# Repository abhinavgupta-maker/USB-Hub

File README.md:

# USB-Hub

# Zine

# Description
So this is my USB Hub 2.0 which has 2x Usb-A and 2x Type-C port and 1x Type-C for upstream which has a retro game controller case which makes it look good and what makes it special is that it is really small like 50 x 30 mm (approx) which makes it really good for storing it.

# How to build it
firstly extract the gerber files of the pcb and upload it on a website and make sure to select PCBA but if you can solder the things on your own then get the pcb only and then get the case 3d printed you can customize it on your own if you want and tehn get it 3d printed.

# Why I built this
For my own usage so that i can extend my ports on the laptop while coding and or playing games.

# Usage
I would use it for for my laptop as it only has 2 USB-A in which one is occupied by cooling stand and other by the mouse so i need to have more ports where i can connect my kbm and my microcontroller while i am coding. and i can use it on my fathers tab to connect a physical keyboard and mouse.

# Schematic

# PCB

# CAD

# BOM

|Product Name        |Product  Link                                                                                                                                                                              |Unit Price|Amount|
|--------------------|-------------------------------------------------------------------------------------------------------------------------------------------------------------------------------------------|----------|------|
|                    |                                                                                                                                                                                           |          |      |
|SMD capacitors 100nF|https://jlcpcb.com/partdetail/YAGEO-CC0603KRX7R9BB104/C14663                                                                                                                               |$0.0094   |11    |
|SMD Resistors 10K   |https://quartzcomponents.com/products/10k-ohm-103-5-smd-resistor-0805-pack-of-20-pieces                                                                                                    |$0.11     |6     |
|SL2.1S              |https://www.lcsc.com/product-detail/C2684433.html?s_z=n_q_SL2.1S&spm=wm.fly.bg.0.xh&lcsc_vid=FQQKBFAFRQVdBABTRQNcBQdWTgRZUlEATgdZAwUHRgMxVlNeRlRcVlVWQ1lfVTsOAxUeFF5JWBYZEEoKFBINSQcJGk4%3D|$9.04     |1     |
|Type-C Port         |https://jlcpcb.com/partdetail/SHOUHAN-TYPEC16PIN/C393939                                                                                                                                   |$0.07     |3     |
|USB-A port          |https://jlcpcb.com/partdetail/SHOUHAN-10_0_QHHTZB63/C668591                                                                                                                                |$0.0662   |2     |
|                    |                                                                                                                                                                                           |          |      |
|                    |Total:                                                                                                                                                                                     |10$ Approx|      |

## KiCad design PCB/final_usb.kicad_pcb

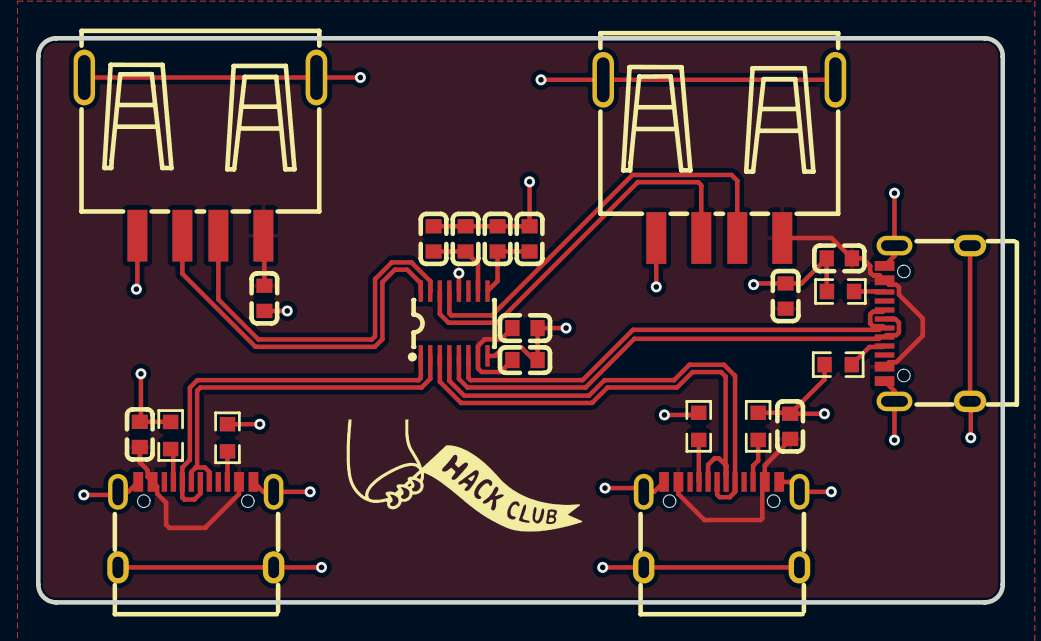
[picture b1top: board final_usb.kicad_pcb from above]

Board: 2 copper layers, 53.6 x 31.3 mm, 23 parts (0 on the bottom side), 20 nets.

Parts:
C1, C2, C3, C4, C5, C6, C7, C8, C9, C10, C11: C0603
R1, R2, R3, R4, R5, R6: R0603
U1: SSOP-16_L4.6-W2.6-P0.53-LS4.0-BL
USB1, USB5, USB6: USB-C-SMD_TYPE-C-16PIN-2MD-073
USB2, USB3: USB-A-TH_10.0QHHTZB6.3

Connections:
$1N1194: R1.2, USB6.A5
$1N1220: R2.2, USB6.B5
$1N1246: R3.2, USB5.A5
$1N1298: R5.2, USB1.B5
$1N1324: R6.2, USB1.A5
$1N2853: C7.1, C8.1, U1.9
$1N2967: C9.1, C10.1, U1.10
$1N3000: R4.2, USB5.B5
+5V: C1.1, C2.1, C3.1, C4.1, C5.1, C6.1, C11.1, U1.7, USB1.A4B9, USB1.B4A9, USB2.1, USB3.1, USB5.A4B9, USB5.B4A9, USB6.A4B9, USB6.B4A9
DM3: U1.15, USB2.2
DM4: U1.13, USB3.2
DN: U1.5, USB1.A7, USB1.B7
DN1: U1.3, USB6.A7, USB6.B7
DN2: U1.1, USB5.A7, USB5.B7
DP: U1.6, USB1.A6, USB1.B6
DP1: U1.4, USB6.A6, USB6.B6
DP2: U1.2, USB5.A6, USB5.B6
DP3: U1.16, USB2.3
DP4: U1.14, USB3.3
GND: C1.2, C2.2, C3.2, C4.2, C5.2, C6.2, C7.2, C8.2, C9.2, C10.2, C11.2, R1.1, R2.1, R3.1, R4.1, R5.1, R6.1, U1.8, U1.12, USB1.13, USB1.14, USB1.A1B12, USB1.B1A12, USB2.4, USB2.5, USB2.6, USB3.4, USB3.5, USB3.6, USB5.13, USB5.14, USB5.A1B12, USB5.B1A12, USB6.13, USB6.14, USB6.A1B12, USB6.B1A12

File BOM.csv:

Reference,Qty,Name,Links
?,1,~,
"C1,C2,C3,C4,C5,C6,C7,C8,C9,C10,C11",11,100nF,https://jlcpcb.com/partdetail/YAGEO-CC0603KRX7R9BB104/C14663
"R1,R2,R3,R4,R5,R6",6,10K,https://jlcpcb.com/partdetail/26547-0603WAF1002T5E/C25804
U1,1,SL2.1s,https://jlcpcb.com/partdetail/CoreChips-SL21s/C2684433
"USB1,USB5,USB6",3,TYPE-C 16PIN 2MD(073), https://jlcpcb.com/partdetail/ShouHan-TYPE_C_16PIN_2MD_073/C2765186
"USB2,USB3",2,10.0 QHHTZB6.3, https://jlcpcb.com/partdetail/10.0%20QHHTZB6.3/C668591

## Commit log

2026-05-23 Rename ProPrj_Usb_Hub_2026-05-23.csv to BOM.csv
2026-06-01 Rename Cyberjunkies.pdf to Zine.pdf
